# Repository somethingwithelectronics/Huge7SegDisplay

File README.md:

View this project on [CADLAB.io](https://cadlab.io/project/2438). 

# Huge7SegDisplay

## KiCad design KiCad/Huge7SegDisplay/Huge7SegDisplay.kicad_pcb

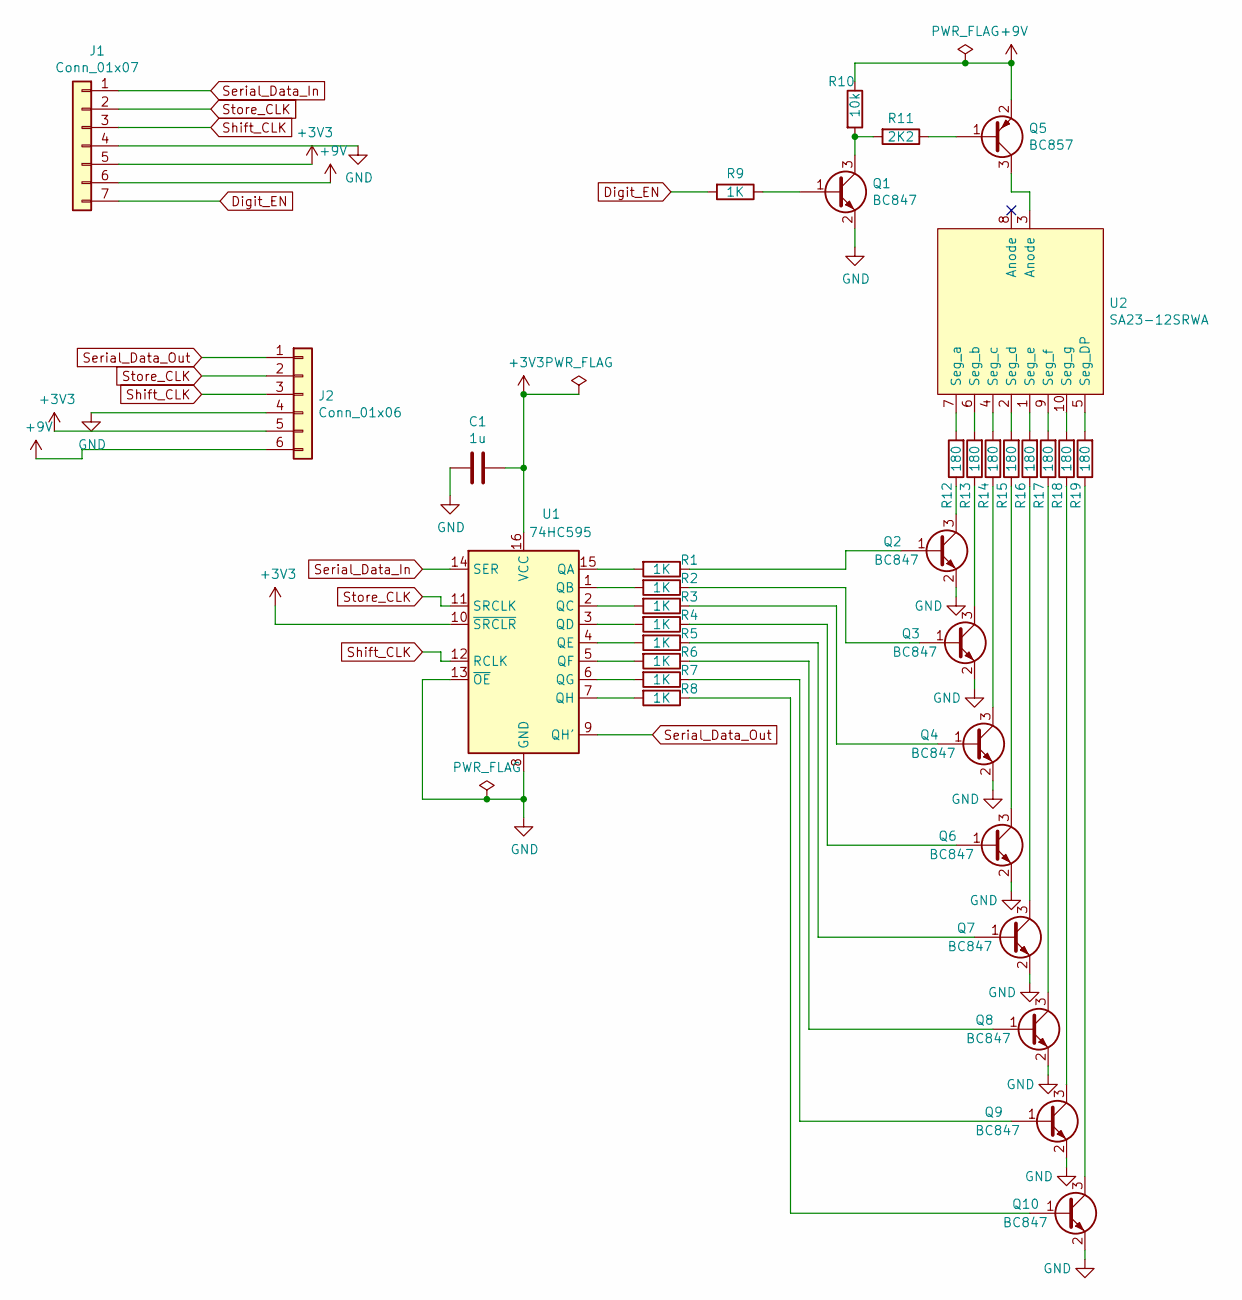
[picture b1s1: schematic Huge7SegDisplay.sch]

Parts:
C1: 1u; C_0805_2012Metric_Pad1.15x1.40mm_HandSolder
J1: Conn_01x07; PinHeader_1x07_P2.54mm_Horizontal_left
J2: Conn_01x06; PinHeader_1x06_P2.54mm_Horizontal
Q1, Q2, Q3, Q4, Q6, Q7, Q8, Q9, Q10: BC847; SOT-23
Q5: BC857; SOT-23
R1, R2, R3, R4, R5, R6, R7, R8, R9: 1K; R_0805_2012Metric_Pad1.15x1.40mm_HandSolder
R10: 10k; R_0805_2012Metric_Pad1.15x1.40mm_HandSolder
R11: 2K2; R_0805_2012Metric_Pad1.15x1.40mm_HandSolder
R12, R13, R14, R15, R16, R17, R18, R19: 180; R_0805_2012Metric_Pad1.15x1.40mm_HandSolder
U1: 74HC595; SOIC-16_3.9x9.9mm_P1.27mm
U2: SA23-12SRWA

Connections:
+3V3: C1.1, J1.5, J2.5, U1.10 (~SRCLR), U1.16 (VCC)
+9V: J1.6, J2.6, Q5.2 (E), R10.1
Digit_EN: J1.7, R9.2
GND: C1.2, J1.4, J2.4, Q1.2 (E), Q2.2 (E), Q3.2 (E), Q4.2 (E), Q6.2 (E), Q7.2 (E), Q8.2 (E), Q9.2 (E), Q10.2 (E), U1.8 (GND), U1.13 (~OE)
unnamed: Q1.1 (B), R9.1
unnamed: Q1.3 (C), R10.2, R11.2
unnamed: Q2.1 (B), R1.1
unnamed: Q2.3 (C), R12.1
unnamed: Q3.1 (B), R2.1
unnamed: Q3.3 (C), R13.1
unnamed: Q4.1 (B), R3.1
unnamed: Q4.3 (C), R14.1
unnamed: Q5.1 (B), R11.1
unnamed: Q5.3 (C), U2.3 (Anode)
unnamed: Q6.1 (B), R4.1
unnamed: Q6.3 (C), R15.1
unnamed: Q7.1 (B), R5.1
unnamed: Q7.3 (C), R16.1
unnamed: Q8.1 (B), R6.1
unnamed: Q8.3 (C), R17.1
unnamed: Q9.1 (B), R7.1
unnamed: Q9.3 (C), R18.1
unnamed: Q10.1 (B), R8.1
unnamed: Q10.3 (C), R19.1
unnamed: R1.2, U1.15 (QA)
unnamed: R2.2, U1.1 (QB)
unnamed: R3.2, U1.2 (QC)
unnamed: R4.2, U1.3 (QD)
unnamed: R5.2, U1.4 (QE)
unnamed: R6.2, U1.5 (QF)
unnamed: R7.2, U1.6 (QG)
unnamed: R8.2, U1.7 (QH)
unnamed: R12.2, U2.7 (Seg_a)
unnamed: R13.2, U2.6 (Seg_b)
unnamed: R14.2, U2.4 (Seg_c)
unnamed: R15.2, U2.2 (Seg_d)
unnamed: R16.2, U2.1 (Seg_e)
unnamed: R17.2, U2.9 (Seg_f)
unnamed: R18.2, U2.10 (Seg_g)
unnamed: R19.2, U2.5 (Seg_DP)
Serial_Data_In: J1.1, U1.14 (SER)
Serial_Data_Out: J2.1, U1.9 (QH')
Shift_CLK: J1.3, J2.3, U1.12 (RCLK)
Store_CLK: J1.2, J2.2, U1.11 (SRCLK)

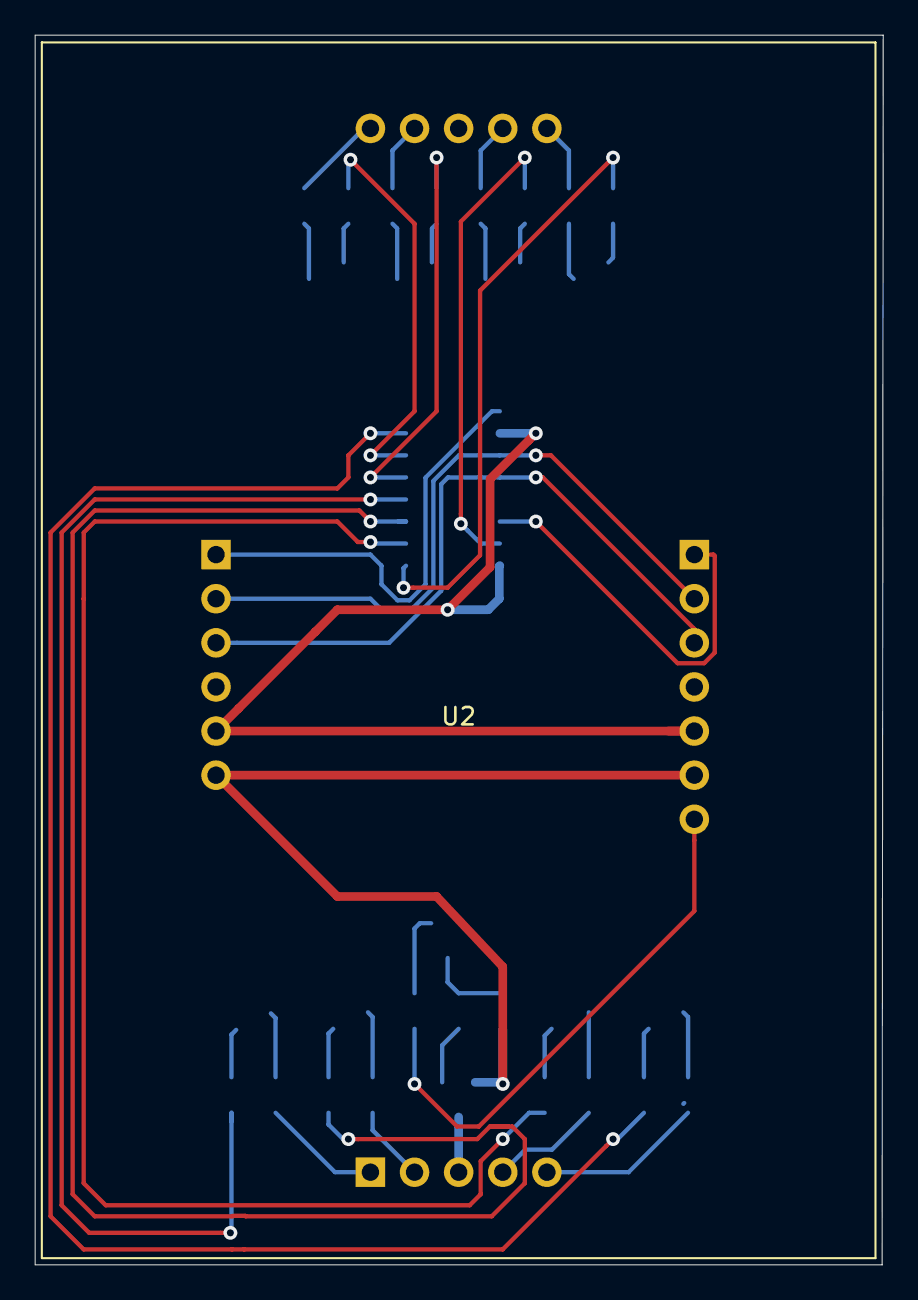
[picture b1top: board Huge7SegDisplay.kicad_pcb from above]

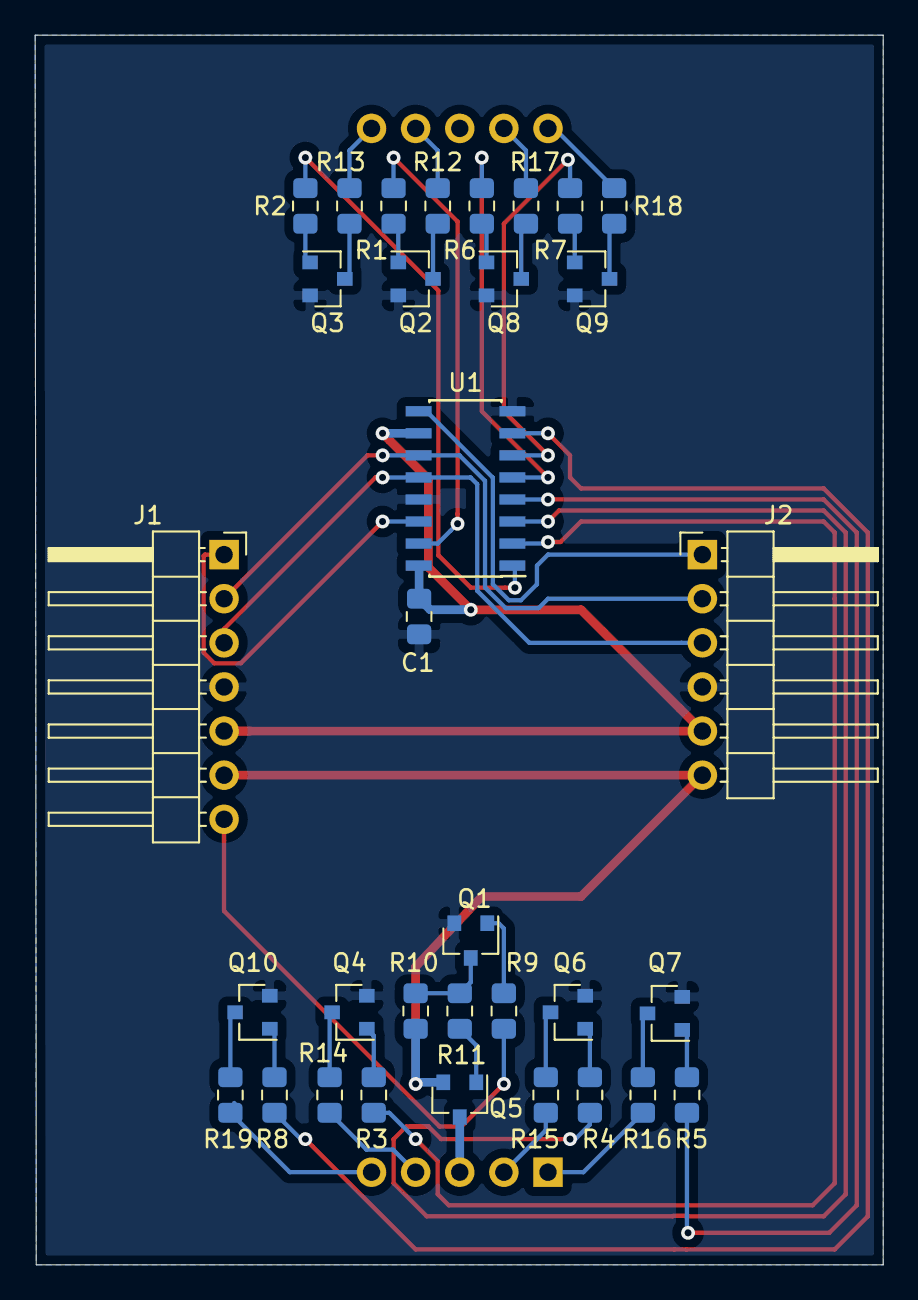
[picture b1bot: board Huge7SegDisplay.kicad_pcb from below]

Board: 2 copper layers, 48.8 x 70.8 mm, 34 parts (33 on the bottom side), 44 nets.

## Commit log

2020-01-27 Backlink to CADLAB.io has been added.
